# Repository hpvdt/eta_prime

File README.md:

# eta_prime
Eta Prime code and circuit CAD

This repository contains all the work done for the electronics for our speedbike Eta Prime.

The main purpose of this system was to implement a video feed with a read out ceratin values imposed of it for the rider to see out of the vechicle. There are two 'versions' of the circuit in this repository:

	Primary one - based on using a raspberry pi and RPi Camera
	Backup - uses a MINIM OSD Module that overlay an OSD to an analog camera feed and passes it on as analog
  
We only currently have the circuitry (designed in EAGLE) for this back system and it is all contained in the "EtaPrimeVisionAnalog" folder. The remaining files are for the primary system which was designed in KiCAD and programmed in python.

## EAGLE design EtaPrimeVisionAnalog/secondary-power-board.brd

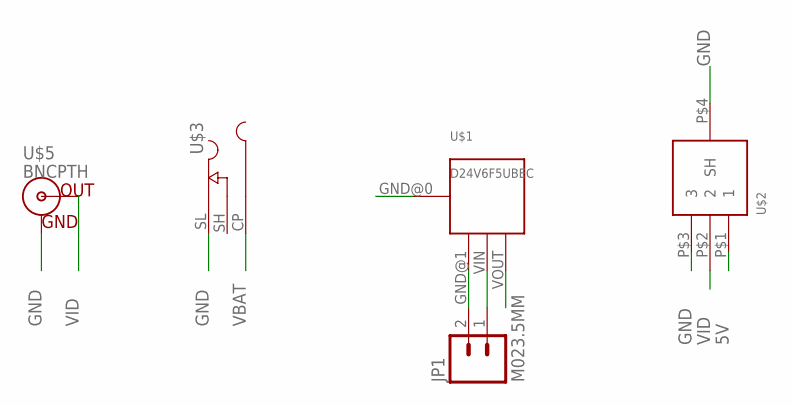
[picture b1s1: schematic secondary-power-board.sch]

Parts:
JP1: M023.5MM; SCREWTERMINAL-3.5MM-2
U$1: D24V6F5UBEC; P2177
U$2: TRA3M
U$3: L722RAS
U$5: BNCPTH; BNC

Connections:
5V: U$1.VOUT, U$2.P$1 (1)
GND: JP1.2, U$1.GND@0, U$1.GND@1, U$2.P$3 (3), U$2.P$4 (SH), U$3.SL (SLEEVE), U$5.GND
VBAT: JP1.1, U$1.VIN, U$3.CP (CENTRE)
VID: U$2.P$2 (2), U$5.S (OUT)

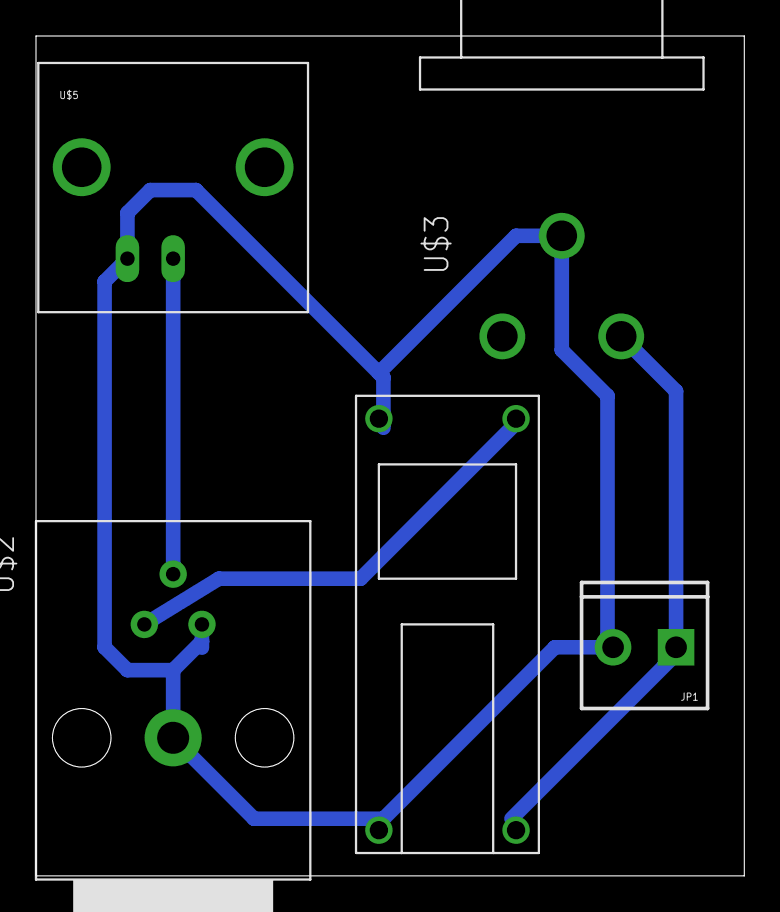
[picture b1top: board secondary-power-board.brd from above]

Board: 2 copper layers, 39.4 x 46.7 mm, 5 parts (0 on the bottom side), 4 nets.

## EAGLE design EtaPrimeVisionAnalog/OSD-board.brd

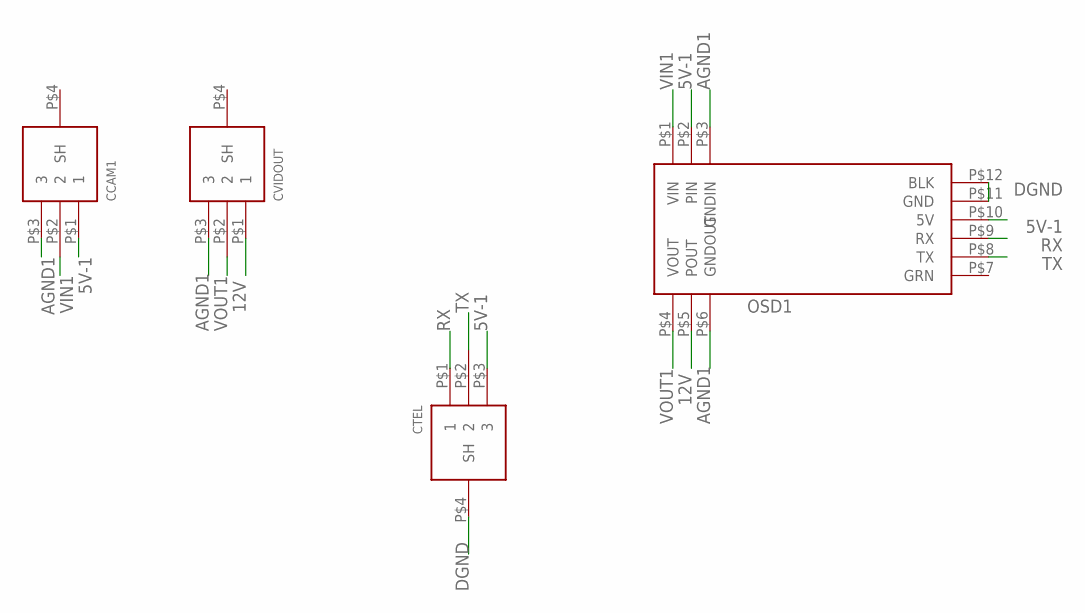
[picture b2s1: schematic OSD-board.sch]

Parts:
CCAM1: TRA3M
CTEL: TRA3MBARE; TRA3M-BARE
CVIDOUT: TRA3M
OSD1: MINIM-OSD

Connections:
5V-1: CCAM1.P$1 (1), CTEL.P$3 (3), OSD1.P$2 (PIN), OSD1.P$10 (5V)
12V: CVIDOUT.P$1 (1), OSD1.P$5 (POUT)
AGND1: CCAM1.P$3 (3), CVIDOUT.P$3 (3), OSD1.P$3 (GNDIN), OSD1.P$6 (GNDOUT)
DGND: CTEL.P$4 (SH), OSD1.P$11 (GND), OSD1.P$12 (BLK)
RX: CTEL.P$1 (1), OSD1.P$9 (RX)
TX: CTEL.P$2 (2), OSD1.P$8 (TX)
VIN1: CCAM1.P$2 (2), OSD1.P$1 (VIN)
VOUT1: CVIDOUT.P$2 (2), OSD1.P$4 (VOUT)

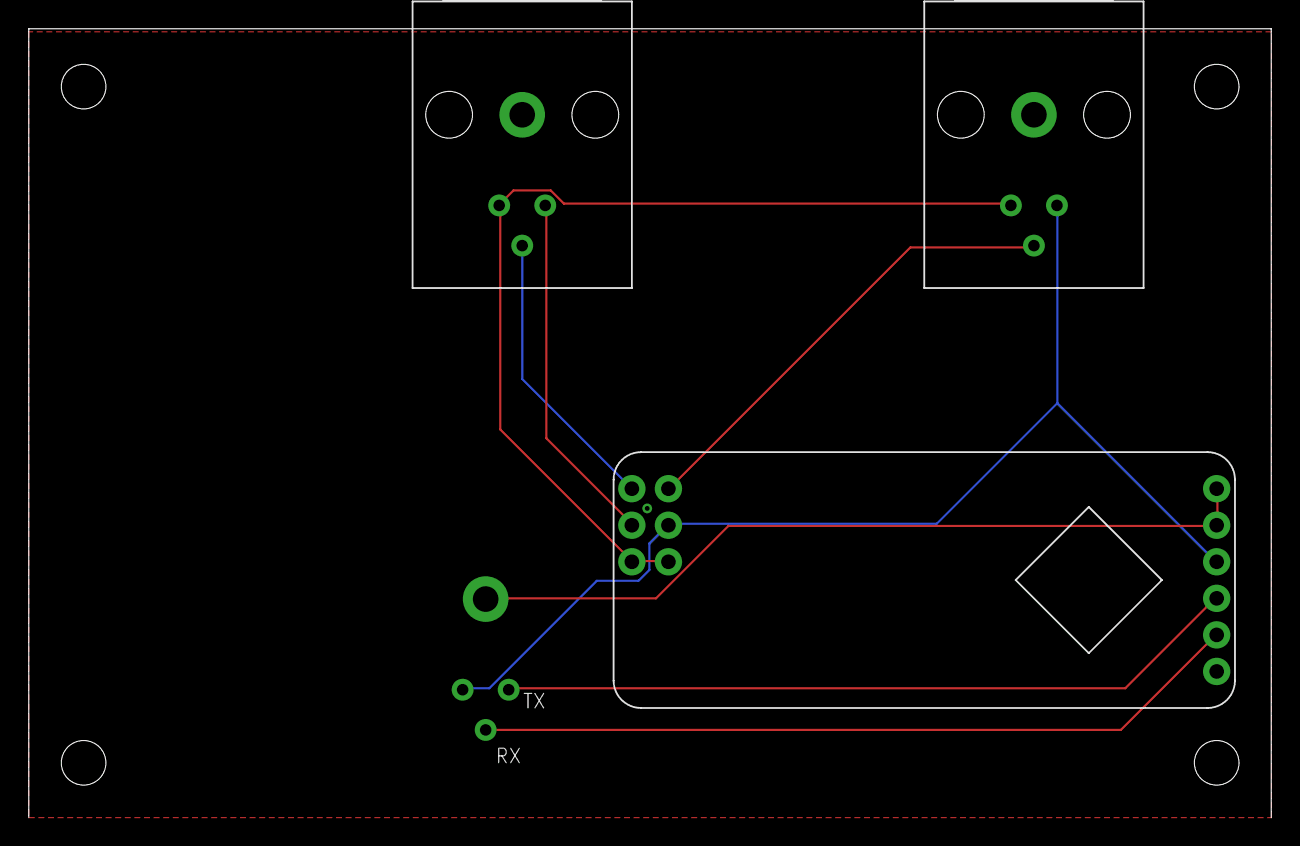
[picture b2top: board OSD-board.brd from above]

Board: 2 copper layers, 86.3 x 54.8 mm, 4 parts (0 on the bottom side), 8 nets.

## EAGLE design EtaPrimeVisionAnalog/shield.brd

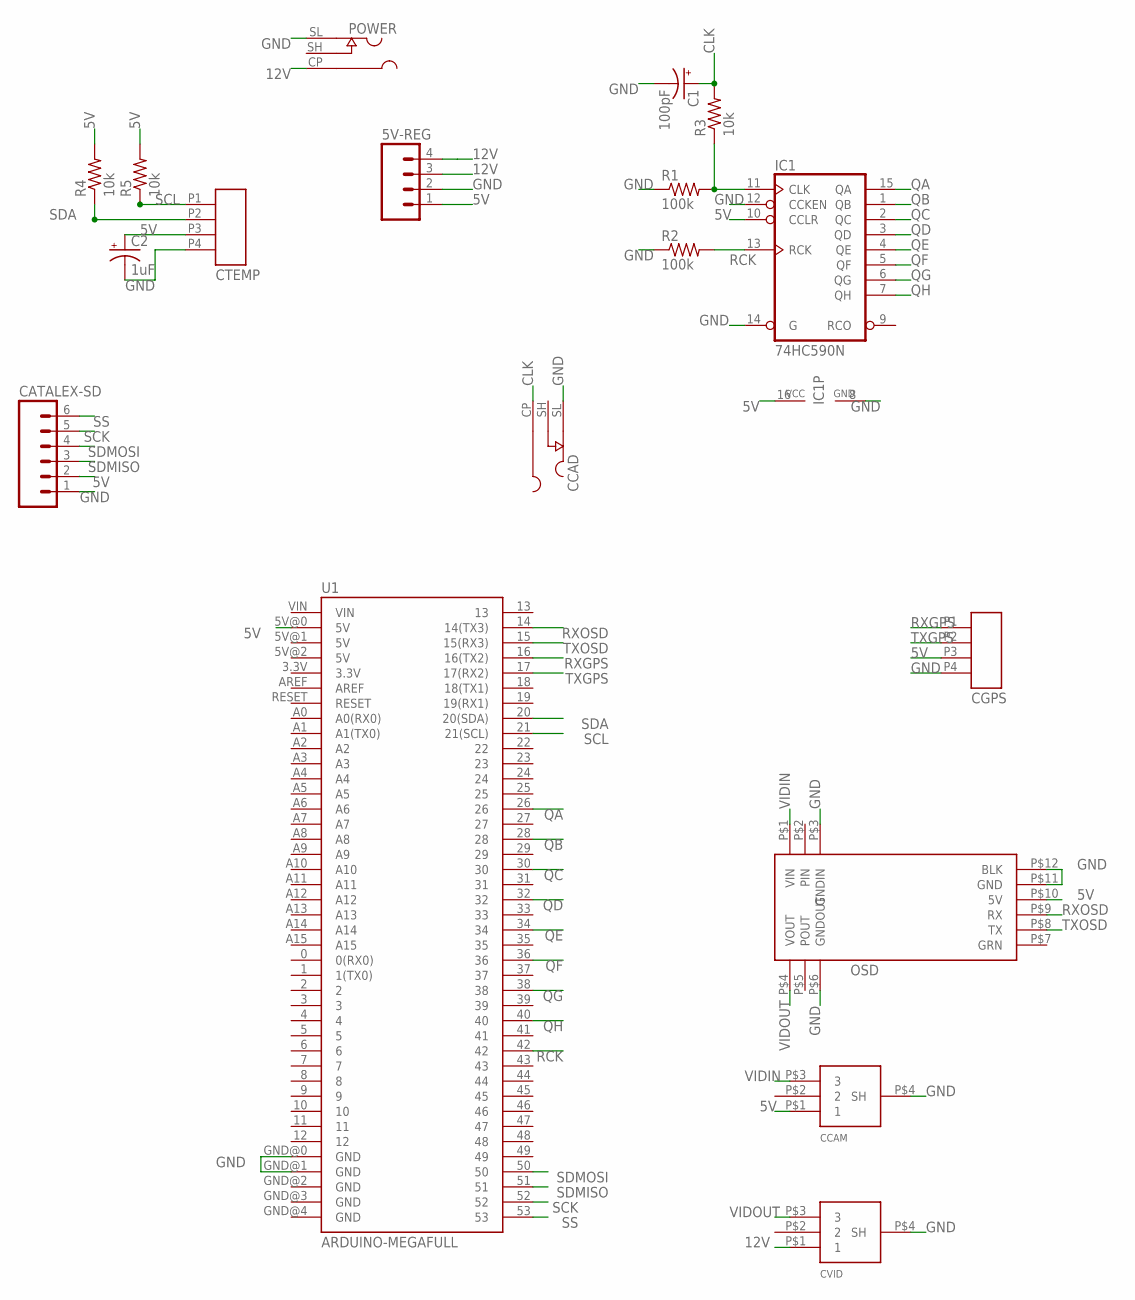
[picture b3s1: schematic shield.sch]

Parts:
5V-REG: M041.27MM; 1X04-1.27MM
C1: 100pF; CPOL-RADIAL-10UF-25V-KIT
C2: 1uF; CPOL-RADIAL-10UF-25V
CATALEX-SD: M06SILK_FEMALE_PTH; 1X06
CCAD: L722RAS
CCAM: TRA3M
CGPS: TRAPC4MSX
CTEMP: TRAPC4MSX
CVID: TRA3M
IC1: 74HC590N; DIL16
OSD: MINIM-OSD
POWER: L722RAS
R1, R2: 100k; AXIAL-0.3EZ
R3, R4, R5: 10k; AXIAL-0.3EZ
U1: ARDUINO-MEGAFULL; ARDUINO_MEGA

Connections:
5V: 5V-REG.1, C2.1 (+), CATALEX-SD.2, CCAM.P$1 (1), CGPS.P3, CTEMP.P3, IC1.10 (CCLR), IC1.16 (VCC), OSD.P$10 (5V), R4.P$2 (2), R5.P$2 (2), U1.5V@0 (5V)
12V: 5V-REG.3, 5V-REG.4, CVID.P$1 (1), POWER.CP (CENTRE)
CLK: C1.1 (+), CCAD.CP (CENTRE), R3.P$2 (2)
GND: 5V-REG.2, C1.2 (-), C2.2 (-), CATALEX-SD.1, CCAD.SL (SLEEVE), CCAM.P$4 (SH), CGPS.P4, CTEMP.P4, CVID.P$4 (SH), IC1.8 (GND), IC1.12 (CCKEN), IC1.14 (G), OSD.P$3 (GNDIN), OSD.P$6 (GNDOUT), OSD.P$11 (GND), OSD.P$12 (BLK), POWER.SL (SLEEVE), R1.P$1 (1), R2.P$1 (1), U1.GND@0 (GND), U1.GND@1 (GND)
unnamed: IC1.11 (CLK), R1.P$2 (2), R3.P$1 (1)
QA: IC1.15 (QA), U1.26
QB: IC1.1 (QB), U1.28
QC: IC1.2 (QC), U1.30
QD: IC1.3 (QD), U1.32
QE: IC1.4 (QE), U1.34
QF: IC1.5 (QF), U1.36
QG: IC1.6 (QG), U1.38
QH: IC1.7 (QH), U1.40
RCK: IC1.13 (RCK), R2.P$2 (2), U1.42
RXGPS: CGPS.P1, U1.16 (16(TX2))
RXOSD: OSD.P$9 (RX), U1.14 (14(TX3))
SCK: CATALEX-SD.5, U1.52
SCL: CTEMP.P1, R5.P$1 (1), U1.21 (21(SCL))
SDA: CTEMP.P2, R4.P$1 (1), U1.20 (20(SDA))
SDMISO: CATALEX-SD.3, U1.51
SDMOSI: CATALEX-SD.4, U1.50
SS: CATALEX-SD.6, U1.53
TXGPS: CGPS.P2, U1.17 (17(RX2))
TXOSD: OSD.P$8 (TX), U1.15 (15(RX3))
VIDIN: CCAM.P$3 (3), OSD.P$1 (VIN)
VIDOUT: CVID.P$3 (3), OSD.P$4 (VOUT)

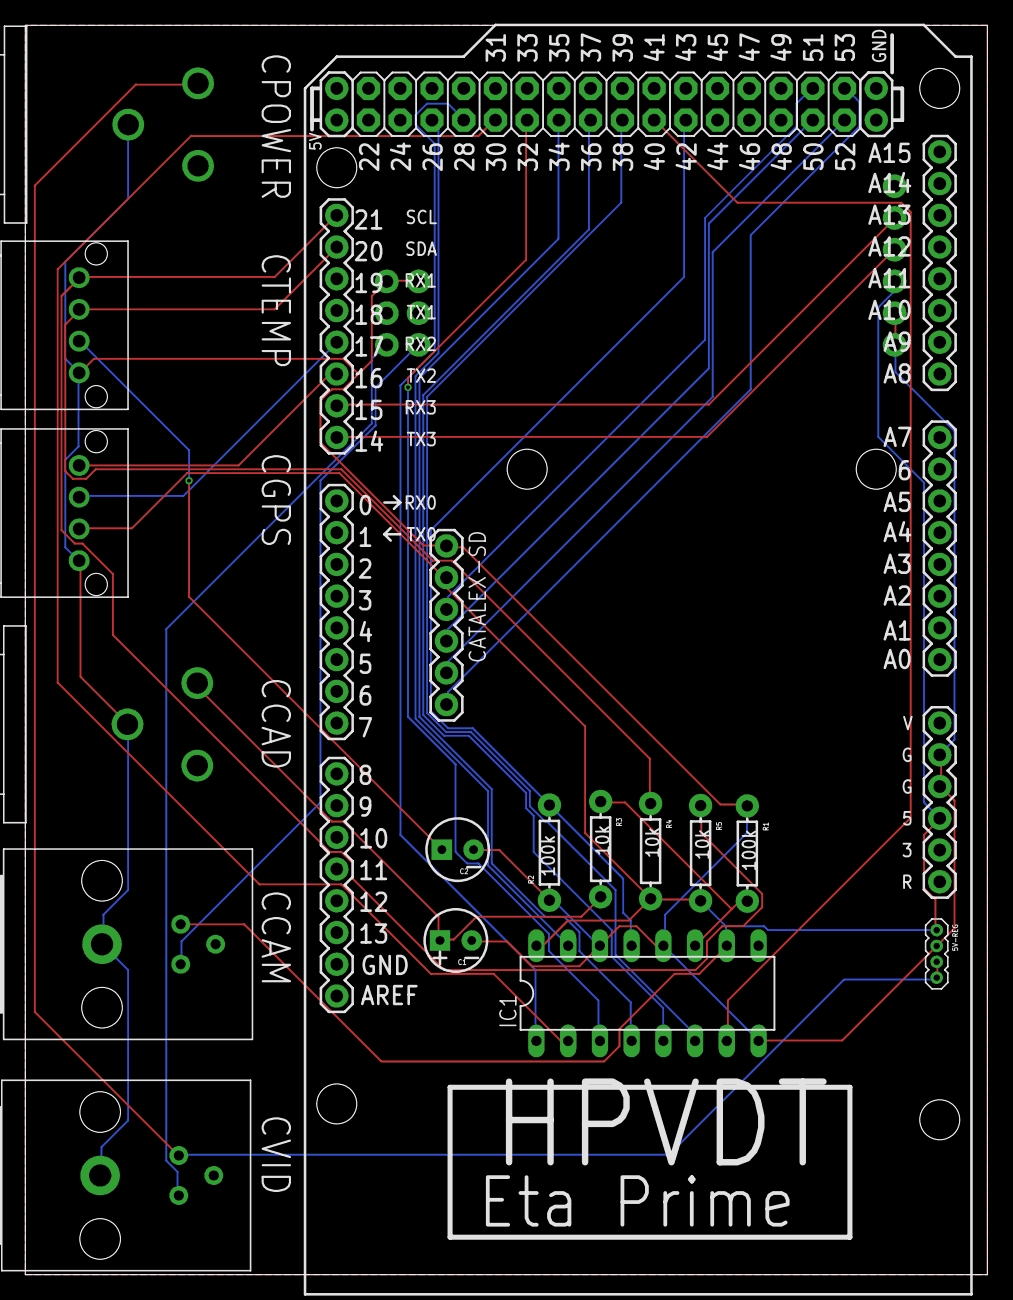
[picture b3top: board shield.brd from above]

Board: 2 copper layers, 77.0 x 100.0 mm, 18 parts (1 on the bottom side), 26 nets.

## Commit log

2019-11-07 Initial Commit
    Upload of the files archived
2019-11-07 Updated README
    Added description of two versions and their associated folders.

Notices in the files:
parts and their libraries:
SparkFun-Connectors: Licensing: CC v3.0 Share-Alike You are welcome to use this library for commercial purposes.
SparkFun-Connectors: Licensing: Creative Commons ShareAlike 4.0 International - https://creativecommons.org/licenses/by-sa/4.0
